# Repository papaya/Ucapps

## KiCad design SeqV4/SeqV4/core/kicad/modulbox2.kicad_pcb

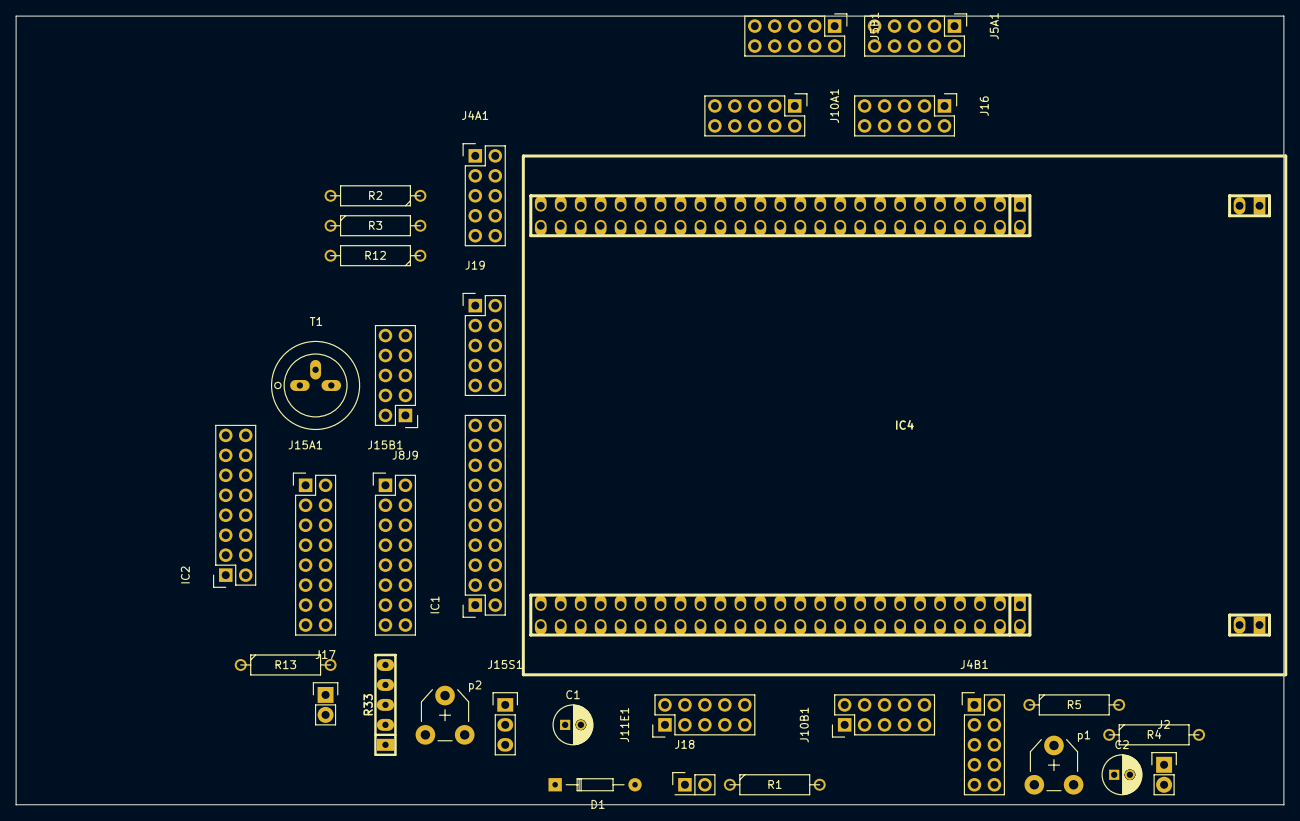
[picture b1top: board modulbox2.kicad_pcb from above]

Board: 2 copper layers, 161.3 x 100.3 mm, 33 parts (0 on the bottom side), 86 nets, no tracks yet.

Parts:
C1, C2: C; C_Radial_D5_L11_P2
D1: D; Diode_DO-35_SOD27_Horizontal_RM10
IC1: 74HCT541_PWR; Socket_Strip_Straight_2x10
IC2: 74HC595; Socket_Strip_Straight_2x08
IC4: STM32F4_Discovery_Header; stm32f4_discovery_header
J2: CONN_2; Pin_Header_Straight_1x02
J4A1, J4B1, J5A1, J5B1, J8J9, J10A1, J10B1, J11E1, J16, J19: CONN_02X05; Pin_Header_Straight_2x05
J15A1, J15B1: CONN_02X08; Pin_Header_Straight_2x08
J15S1: CONN_01X03; Pin_Header_Straight_1x03
J17: CONN_01X02; Pin_Header_Straight_1x02
J18: CONN_2; Pin_Header_Straight_2x01
R1, R2, R3, R4, R5, R12, R13: R; R4-5
R33: R-SIL_4; r-sil_5
T1: BC817-40; OldSowjetaera_Transistor_Type-II_BigPads
p1, p2: POT; Potentiometer_VishaySpectrol-Econtrim-Type36T

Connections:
+3V3: IC4.3, IC4.4, IC4.80, IC4.95, J5A1.2, J5B1.2, J10A1.2, J10B1.2, J11E1.2, J15S1.3, J16.3, J16.4
+5V: C2.2, IC1.20, IC4.97, IC4.98, J2.1, J4A1.10, J4B1.10, J8J9.3, J8J9.4, J15A1.1, J15B1.1, J15S1.1, J17.1, J19.3, J19.4, R1.2, R2.1, R3.2, R4.1, R5.2, R12.1, p1.1
/PA1: IC4.11, J5A1.8
/PA2: IC4.14, J11E1.8
/PA3: IC4.13, J11E1.4
/PA4: IC4.16, J5A1.10
/PA5: IC4.15, J16.7, J16.8
/PA6: IC4.18, J16.5
/PA7: IC4.17, J16.6
/PA8: IC2.14, IC4.57, J15A1.14, J15B1.14, R33.2
/PA9: IC4.58, J17.2
/PA15: IC1.3, IC4.62
/PB0: IC4.22, J5B1.8
/PB1: IC4.21, J5B1.10
/PB2: IC4.24, J16.10
/PB3: IC1.4, IC4.74
/PB4: IC4.75, J19.5
/PB5: IC1.5, IC4.76
/PB6: IC4.77, J4B1.6, R4.2
/PB7: IC4.78, J11E1.6
/PB8: IC1.2, IC4.81
/PB9: IC4.82, J4B1.8, R5.1
/PB10: IC4.34, J4A1.6, R2.2
/PB11: IC4.35, J4A1.8, R3.1
/PB12: IC1.7, IC4.36
/PB13: IC1.8, IC4.37
/PB14: IC4.38, J8J9.5
/PB15: IC1.9, IC4.39
/PC1: IC4.7, J5A1.4
/PC2: IC4.10, J5A1.6
/PC4: IC4.20, J5B1.4
/PC5: IC4.19, J5B1.6
/PC6: IC4.53, J11E1.10
/PC8: IC4.55, J15A1.12, R33.3, p2.2
/PC9: IC4.56, J15B1.12, R33.4
/PC11: IC2.13, IC4.64, J15A1.11, J15B1.11, R33.5
/PC12: IC4.65, J11E1.9
/PC13: IC4.90, J10B1.3
/PC14: IC4.91, J10B1.4
/PC15: IC4.92, J10B1.5
/PD0: D1.2, IC4.66, J18.2, R1.1
/PD1: D1.1, IC4.67
/PD2: IC4.68, J11E1.5
/PD3: IC2.12, IC4.69
/PD6: IC2.11, IC4.72
/PD7: IC2.7, IC4.73, J15A1.4, J15B1.4
/PD8: IC4.40, J11E1.7
/PD9: IC4.41, J11E1.3
/PD10: IC1.6, IC4.42
/PD11: IC4.43, J16.9
/PE2: IC4.85, J10B1.6
/PE4: IC4.87, J10B1.7
/PE5: IC4.88, J10B1.8
/PE6: IC4.89, J10B1.9
/PE7: IC4.25, J10B1.10
/PE8: IC4.26, J10A1.3
/PE9: IC4.27, J10A1.4
/PE10: IC4.28, J10A1.5
/PE11: IC4.29, J10A1.6
/PE12: IC4.30, J10A1.7
/PE13: IC4.31, J10A1.8
/PE14: IC4.32, J10A1.9
/PE15: IC4.33, J10A1.10
GND: C1.2, C2.1, IC1.1, IC1.10, IC1.19, IC2.8, IC4.1, IC4.2, IC4.5, IC4.23, IC4.49, IC4.50, IC4.51, IC4.52, IC4.99, IC4.100, J2.2, J4A1.1, J4A1.2, J4A1.3, J4A1.4, J4A1.5, J4A1.7, J4A1.9, J4B1.1, J4B1.2, J4B1.3, J4B1.4, J4B1.5, J4B1.7, J4B1.9, J5A1.1, J5B1.1, J8J9.1, J8J9.2, J10A1.1, J10B1.1, J11E1.1, J15A1.15, J15B1.15, J16.1, J16.2, J18.1, J19.1, J19.2, T1.2, p1.3, p2.3
unnamed: C1.1, IC2.10, IC2.16, J15A1.16, J15B1.16, J15S1.2, R33.1, p2.1
unnamed: IC1.11, J8J9.6
unnamed: IC1.12, J8J9.7, J8J9.8
unnamed: IC1.13, J8J9.10
unnamed: IC1.14, J8J9.9
unnamed: IC1.15, J19.6
unnamed: IC1.16, J19.7, J19.8
unnamed: IC1.17, J19.10
unnamed: IC1.18, J19.9
unnamed: IC2.1, J15A1.10, J15B1.10
unnamed: IC2.2, J15A1.7, J15B1.7
unnamed: IC2.3, J15A1.8, J15B1.8
unnamed: IC2.4, J15A1.5, J15B1.5
unnamed: IC2.5, J15A1.6, J15B1.6
unnamed: IC2.6, J15A1.3, J15B1.3
unnamed: IC2.15, J15A1.9, J15B1.9
unnamed: J5A1.3, J5A1.5, J5A1.7, J5A1.9
unnamed: J5B1.3, J5B1.5, J5B1.7, J5B1.9
unnamed: J15A1.2, J15B1.2, R12.2, T1.3
unnamed: J15A1.13, J15B1.13
unnamed: R13.1, p1.2
unnamed: R13.2, T1.1

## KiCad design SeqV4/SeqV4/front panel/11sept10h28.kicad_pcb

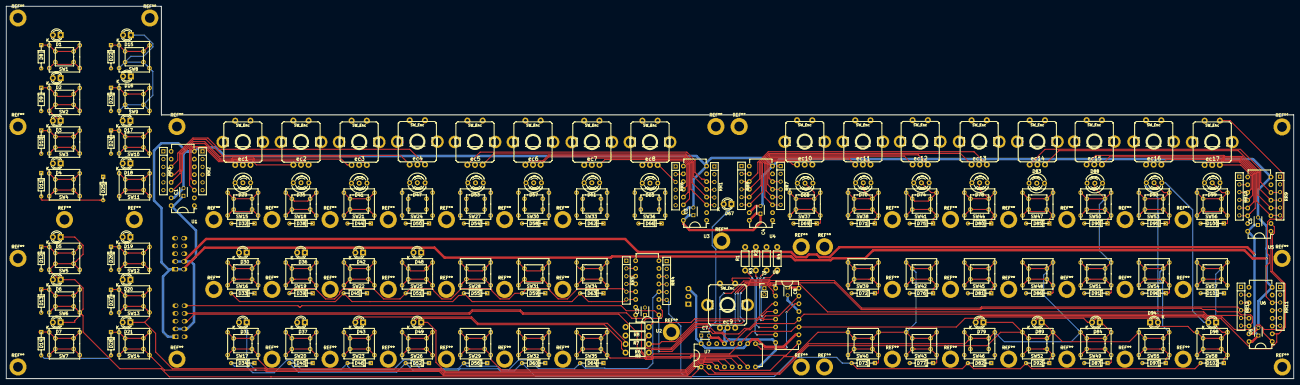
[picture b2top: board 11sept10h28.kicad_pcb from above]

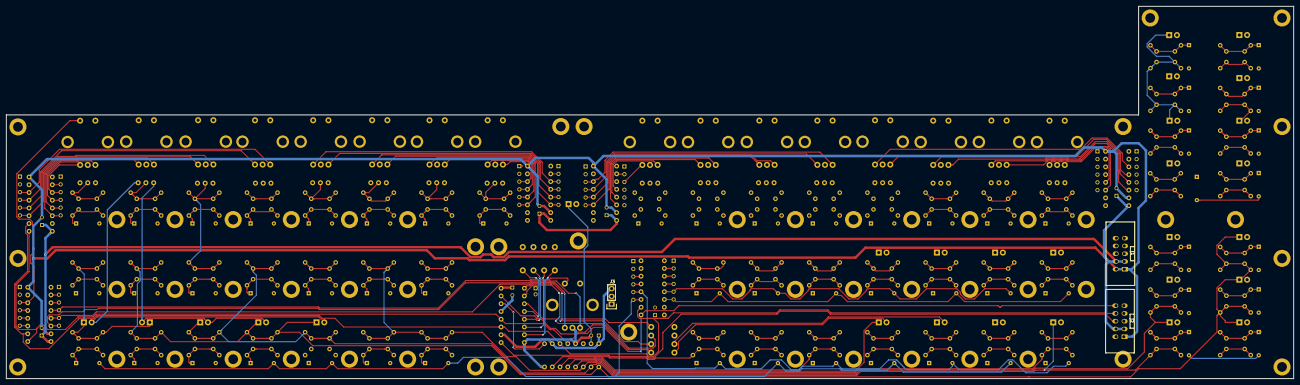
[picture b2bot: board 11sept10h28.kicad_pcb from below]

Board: 2 copper layers, 421.6 x 121.9 mm, 217 parts (3 on the bottom side), 147 nets.

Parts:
C1, C2, C3, C4, C5, C6, C7, C8: C; C_Disc_D3_P2.5
D1: LED trck gr 1; LED-3MM
D2: LED trck gr 2; LED-3MM
D3: LED_trck_gr_3; LED-3MM
D4: LED_trck_gr_4; LED-3MM
D5: LED_trg_ly_a; LED-3MM
D6: LED_trg_ly_b; LED-3MM
D7: LED_trg_ly_c; LED-3MM
D8, D9, D10, D11, D12, D13, D14, D22, D23, D24, D25, D26, D27, D28, D32, D33, D34, D38, D39, D40, D44, D45, D46, D50, D51, D52, D54, D55, D56, D58, D59, D60, D62, D63, D64, D66, D69, D71, D72, D73, D75, D76, D77, D80, D81, D82, D85, D86, D87, D90, D91, D92, D95, D96, D97, D100, D101, D102: D; DO-35
D15: LED trck 1; LED-3MM
D16: LED trck 2; LED-3MM
D17: LED trck 3; LED-3MM
D18: LED trck 4; LED-3MM
D19: LED_prm_ly_a; LED-3MM
D20: LED_prm_ly_b; LED-3MM
D21: LED_prm_ly_c; LED-3MM
D29: Led_gp1; LED-5MM-3
D30: LED edit; LED-3MM
D31: LED step view; LED-3MM
D35: Led_gp2; LED-5MM-3
D36: LED mute; LED-3MM
D37: LED solo; LED-3MM
D41: Led_gp3; LED-5MM-3
D42: LED patern; LED-3MM
D43: LED fast; LED-3MM
D47: Led_gp4; LED-5MM-3
D48: LED song; LED-3MM
D49: LED all; LED-3MM
D53: Led_gp5; LED-5MM-3
D57: Led_gp6; LED-5MM-3
D61: Led_gp7; LED-5MM-3
D65: Led_gp8; LED-5MM-3
D67: LED beat; LED-3MM
D68: Led_gp9; LED-5MM-3
D70: Led_gp10; LED-5MM-3
D74: Led_gp11; LED-5MM-3
D78: Led_gp12; LED-5MM-3
D79: LED rwd; LED-3MM
D83: Led_gp13; LED-5MM-3
D84: LED stop; LED-3MM
D88: Led_gp14; LED-5MM-3
D89: LED pause; LED-3MM
D93: Led_gp15; LED-5MM-3
D94: LED play; LED-3MM
D98: LED fwd; LED-3MM
D99: Led_gp16; LED-5MM-3
J3: CONN_01X03; Pin_Header_Straight_1x03
R1, R3: 470ohm; Resistor_Horizontal_RM7mm
R2, R4: 1k; Resistor_Horizontal_RM7mm
R5, R6, R7, R8: r220; Resistor_Horizontal_RM7mm
RR1, RR2, RR3, RR4, RR5, RR6, RR7, RR8, RR9, RR10, RR11, RR12: 5x10k; Resistor_Array_SIP6
SW1: SW_trck_gr_1; multibp_ks
SW2: SW_trck_gr_2; multibp_ks
SW3: SW_trck_gr_3; multibp_ks
SW4: SW_trck_gr_4; multibp_ks
SW5: SW_trg_ly_a; multibp_ks
SW6: SW_trg_ly_b; multibp_ks
SW7: SW_trg_ly_c; multibp_ks
SW8: SW_trck_1; multibp_ks
SW9: SW_trck_2; multibp_ks
SW10: SW_trck_3; multibp_ks
SW11: SW_trck_4; multibp_ks
SW12: SW_prm_ly_a; multibp_ks
SW13: SW_prm_ly_b; multibp_ks
SW14: SW_prm_ly_c; multibp_ks
SW15: SW_mixer_GP1; multibp_ks
SW16: SW_edit; multibp_ks
SW17: SW_step_view; multibp_ks
SW18: SW_event_GP2; multibp_ks
SW19: SW_mute; multibp_ks
SW20: SW_solo; multibp_ks
SW21: SW_mode_GP3; multibp_ks
SW22: SW_pattern; multibp_ks
SW23: SW_fast; multibp_ks
SW24: SW_direction_GP4; multibp_ks
SW25: SW_song; multibp_ks
SW26: SW_all; multibp_ks
SW27: SW_diyder_GP5; multibp_ks
SW28: SW_copy; multibp_ks
SW29: SW_menu; multibp_ks
SW30: SW_length_GP6; multibp_ks
SW31: SW_paste; multibp_ks
SW32: SW_select; multibp_ks
SW33: SW_transpose_GP7; multibp_ks
SW34: SW_clear; multibp_ks
SW35: SW_exit; multibp_ks
SW36: SW_grooove_GP8; multibp_ks
SW37: SW_trigger_GP9; multibp_ks
SW38: SW_fx_GP10; multibp_ks
SW39: SW_down; multibp_ks
SW40: SW_scrub; multibp_ks
SW41: SW_manual_GP11; multibp_ks
SW42: SW_up; multibp_ks
SW43: SW_metronome; multibp_ks
SW44: SW_morph_GP12; multibp_ks
SW45: SW_utility; multibp_ks
SW46: SW_reward; multibp_ks
SW47: SW_bpm_GP13; multibp_ks
SW48: SW_f1; multibp_ks
SW49: SW_stop; multibp_ks
SW50: SW_save_GP14; multibp_ks
SW51: SW_f2; multibp_ks
SW52: SW_pause; multibp_ks
SW53: SW_midi_GP15; multibp_ks
SW54: SW_f3; multibp_ks
SW55: SW_play; multibp_ks
SW56: SW_sys ex_GP16; multibp_ks
SW57: SW_f4; multibp_ks
SW58: SW_forward; multibp_ks
U1, U2, U3, U4, U5, U6: 74HC165; DIP-16_W7.62mm
U7, U8: 74HC595PWR; DIP-16_W7.62mm
ec1, ec2, ec3, ec4, ec5, ec6, ec7, ec8, ec9, ec10, ec11, ec12, ec13, ec14, ec15, ec16, ec17: SW_Enc; PEC11-Switch_ba
j1, j2: CONN_02X05; vasch_strip_5x2
j5: CONN_01X02; Pin_Header_Straight_1x02_Pitch2.00mm

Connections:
+5V: C1.1, C2.1, C3.1, C4.1, C5.1, C6.1, C7.1, C8.1, J3.3, U1.16, U2.16, U3.16, U4.16, U5.16, U6.16, U7.10, U7.16, U8.10, U8.16, j1.3, j1.4, j2.3, j2.4, j5.1
/02: D36.1, D42.1, D43.1, D48.1, D49.1, U7.5
/011: D29.1, D53.1, D68.1, D83.1, R2.2
/012: D35.3, D57.3, D70.3, D88.3, R3.2
/I0: RR3.3, U1.11, ec4.P$A
/I1: RR3.4, U1.12, ec4.P$B
/I2: RR3.5, U1.13, ec3.P$A
/I3: RR3.6, U1.14, ec3.P$B
/I4: RR2.6, U1.3, ec2.P$A
/I5: RR2.5, U1.4, ec2.P$B
/I6: RR2.4, U1.5, ec1.P$A
/I7: RR2.3, U1.6, ec1.P$B
/I10: D32.2, D44.2, D54.2, D62.2, D69.2, D75.2, D85.2, D95.2, RR5.3, U2.11
/I11: D38.2, D50.2, D58.2, D66.2, D71.2, D80.2, D90.2, D100.2, RR5.4, U2.12
/I12: D39.2, D51.2, D59.2, D72.2, D81.2, D91.2, D101.2, RR5.5, U2.13
/I13: D33.2, D45.2, D55.2, D63.2, D76.2, D86.2, D96.2, RR5.6, U2.14
/I14: D40.2, D52.2, D60.2, D73.2, D82.2, D92.2, D102.2, RR4.6, U2.3
/I15: D34.2, D46.2, D56.2, D64.2, D77.2, D87.2, D97.2, RR4.5, U2.4
/I16: D8.2, D10.2, D12.2, D14.2, D22.2, D24.2, D26.2, D28.2, RR4.4, U2.5
/I17: D9.2, D11.2, D13.2, D23.2, D25.2, D27.2, RR4.3, U2.6
/I20: RR6.3, U3.11, ec8.P$A
/I21: RR6.4, U3.12, ec8.P$B
/I22: RR6.5, U3.13, ec7.P$A
/I23: RR6.6, U3.14, ec7.P$B
/I24: RR1.6, U3.3, ec6.P$A
/I25: RR1.5, U3.4, ec6.P$B
/I26: RR1.4, U3.5, ec5.P$A
/I27: RR1.3, U3.6, ec5.P$B
/I30: RR8.3, U4.11, ec13.P$A
/I31: RR8.4, U4.12, ec13.P$B
/I32: RR8.5, U4.13, ec12.P$A
/I33: RR8.6, U4.14, ec12.P$B
/I34: RR7.6, U4.3, ec11.P$A
/I35: RR7.5, U4.4, ec11.P$B
/I36: RR7.4, U4.5, ec10.P$A
/I37: RR7.3, U4.6, ec10.P$B
/I40: RR10.3, U5.11, ec17.P$A
/I41: RR10.4, U5.12, ec17.P$B
/I42: RR10.5, U5.13, ec16.P$A
/I43: RR10.6, U5.14, ec16.P$B
/I44: RR9.6, U5.3, ec15.P$A
/I45: RR9.5, U5.4, ec15.P$B
/I46: RR9.4, U5.5, ec14.P$A
/I47: RR9.3, U5.6, ec14.P$B
/I50: RR12.3, U6.11
/I51: RR12.4, U6.12, ec9.P$2
/I52: RR12.5, U6.13, ec9.P$A
/I53: RR12.6, U6.14, ec9.P$B
/I54: RR11.6, U6.3
/I55: RR11.5, U6.4
/I56: RR11.4, U6.5
/I57: RR11.3, U6.6, ec1.P$2, ec2.P$2, ec3.P$2, ec4.P$2, ec5.P$2, ec6.P$2, ec7.P$2, ec8.P$2, ec10.P$2, ec11.P$2, ec12.P$2, ec13.P$2, ec14.P$2, ec15.P$2, ec16.P$2, ec17.P$2
/O0: D1.1, D2.1, D3.1, D4.1, D61.2, D65.2, SW1.2, SW2.2, SW31.2, SW32.2, SW33.2, SW34.2, SW35.2, SW36.2, U7.7
/O1: D15.1, D17.1, D53.2, D57.2, SW8.2, SW9.2, SW25.2, SW26.2, SW27.2, SW28.2, SW29.2, SW30.2, U7.6
/O2: D37.1, D41.2, D47.2, SW3.2, SW4.2, SW19.2, SW20.2, SW21.2, SW22.2, SW23.2, SW24.2
/O3: D16.1, D18.1, D29.2, D30.1, D35.2, SW10.2, SW11.2, SW15.2, SW16.2, SW17.2, SW18.2, U7.4
/O4: D19.1, D20.1, D21.1, D68.2, D70.2, SW12.2, SW13.2, SW37.1, SW38.1, SW39.1, SW40.1, SW42.1, SW43.1, U7.3
/O5: D31.1, D74.2, D78.2, D84.1, SW14.2, SW41.1, SW44.1, SW45.1, SW46.1, SW48.1, SW49.1, U7.2
/O6: D5.1, D6.1, D7.1, D79.1, D83.2, D88.2, D89.1, SW5.2, SW6.2, SW47.1, SW50.1, SW51.1, SW52.1, SW54.1, SW55.1, U7.1
/O7: D67.1, D93.2, D94.1, D98.1, D99.2, SW7.2, SW53.1, SW56.1, SW57.1, SW58.1, U7.15
/O10: D29.3, D53.3, D68.3, D83.3, R1.2
/O13: D35.1, D57.1, D70.1, D88.1, R4.2
/O14: D1.2, D30.2, D36.2, D41.3, D42.2, D61.3, D74.3, D84.2, D89.2, D93.3, D94.2, R8.2
/O15: D2.2, D5.2, D16.2, D17.2, D19.2, D41.1, D48.2, D61.1, D74.1, D79.2, D93.1, D98.2, R7.2
/O16: D3.2, D6.2, D15.2, D18.2, D20.2, D31.2, D37.2, D43.2, D47.3, D65.3, D78.3, D99.3, R6.2
/O17: D4.2, D7.2, D21.2, D47.1, D49.2, D65.1, D67.2, D78.1, D99.1, R5.1
GND: C1.2, C2.2, C3.2, C4.2, C5.2, C6.2, C7.2, C8.2, J3.1, U1.8, U1.15, U2.8, U2.15, U3.8, U3.15, U4.8, U4.15, U5.8, U5.15, U6.8, U6.15, U7.8, U7.13, U8.8, U8.13, ec1.P$1, ec1.P$C, ec2.P$1, ec2.P$C, ec3.P$1, ec3.P$C, ec4.P$1, ec4.P$C, ec5.P$1, ec5.P$C, ec6.P$1, ec6.P$C, ec7.P$1, ec7.P$C, ec8.P$1, ec8.P$C, ec9.P$1, ec9.P$C, ec9.P$GN, ec10.P$1, ec10.P$C, ec11.P$1, ec11.P$C, ec12.P$1, ec12.P$C, ec13.P$1, ec13.P$C, ec14.P$1, ec14.P$C, ec15.P$1, ec15.P$C, ec16.P$1, ec16.P$C, ec17.P$1, ec17.P$C, j1.1, j1.2, j2.1, j2.2, j5.2
unnamed: D8.1, SW1.1
unnamed: D9.1, SW2.1
unnamed: D10.1, SW3.1
unnamed: D11.1, SW4.1
unnamed: D12.1, SW5.1
unnamed: D13.1, SW6.1
unnamed: D14.1, SW7.1
unnamed: D22.1, SW8.1
unnamed: D23.1, SW9.1
unnamed: D24.1, SW10.1
unnamed: D25.1, SW11.1
unnamed: D26.1, SW12.1
unnamed: D27.1, SW13.1
unnamed: D28.1, SW14.1
unnamed: D32.1, SW15.1
unnamed: D33.1, SW16.1
unnamed: D34.1, SW17.1
unnamed: D38.1, SW18.1
unnamed: D39.1, SW19.1
unnamed: D40.1, SW20.1
unnamed: D44.1, SW21.1
unnamed: D45.1, SW22.1
unnamed: D46.1, SW23.1
unnamed: D50.1, SW24.1
unnamed: D51.1, SW25.1
unnamed: D52.1, SW26.1
unnamed: D54.1, SW27.1
unnamed: D55.1, SW28.1
unnamed: D56.1, SW29.1
unnamed: D58.1, SW30.1
unnamed: D59.1, SW31.1
unnamed: D60.1, SW32.1
unnamed: D62.1, SW33.1
unnamed: D63.1, SW34.1
unnamed: D64.1, SW35.1
unnamed: D66.1, SW36.1
unnamed: D69.1, SW37.2
unnamed: D71.1, SW38.2
unnamed: D72.1, SW39.2
unnamed: D73.1, SW40.2
unnamed: D75.1, SW41.2
unnamed: D76.1, SW42.2
unnamed: D77.1, SW43.2
unnamed: D80.1, SW44.2
unnamed: D81.1, SW45.2
unnamed: D82.1, SW46.2
unnamed: D85.1, SW47.2
unnamed: D86.1, SW48.2
unnamed: D87.1, SW49.2
unnamed: D90.1, SW50.2
unnamed: D91.1, SW51.2
unnamed: D92.1, SW52.2
unnamed: D95.1, SW53.2
unnamed: D96.1, SW54.2
unnamed: D97.1, SW55.2
unnamed: D100.1, SW56.2
unnamed: D101.1, SW57.2
unnamed: D102.1, SW58.2
unnamed: J3.2, RR1.1, RR2.1, RR3.1, RR4.1, RR5.1, RR6.1, RR7.1, RR8.1, RR9.1, RR10.1, RR11.1, RR12.1
unnamed: R1.1, U8.7
unnamed: R2.1, U8.6
unnamed: R3.1, U8.5
unnamed: R4.1, U8.4
unnamed: R5.2, U8.15
unnamed: R6.1, U8.1
unnamed: R7.1, U8.2
unnamed: R8.1, U8.3
unnamed: RR3.2, U1.10, U2.9
unnamed: RR5.2, U2.10, U3.9
unnamed: RR6.2, U3.10, U4.9
unnamed: RR8.2, U4.10, U6.9
unnamed: RR10.2, U5.10, j2.5
unnamed: RR12.2, U5.9, U6.10
unnamed: U1.1, U2.1, U3.1, U4.1, U5.1, U6.1, U7.12, U8.12, j1.10, j2.10
unnamed: U1.2, U2.2, U3.2, U4.2, U5.2, U6.2, U7.11, U8.11, j1.7, j1.8, j2.7, j2.8
unnamed: U1.9, j1.5
unnamed: U7.9, U8.14
unnamed: U7.14, j1.6
unnamed: U8.9, j2.6
unnamed: ec1.P$GN, ec2.P$GN, ec3.P$GN, ec4.P$GN, ec5.P$GN, ec6.P$GN, ec7.P$GN, ec8.P$GN, ec10.P$GN, ec11.P$GN, ec12.P$GN, ec13.P$GN, ec14.P$GN, ec15.P$GN, ec16.P$GN, ec17.P$GN
